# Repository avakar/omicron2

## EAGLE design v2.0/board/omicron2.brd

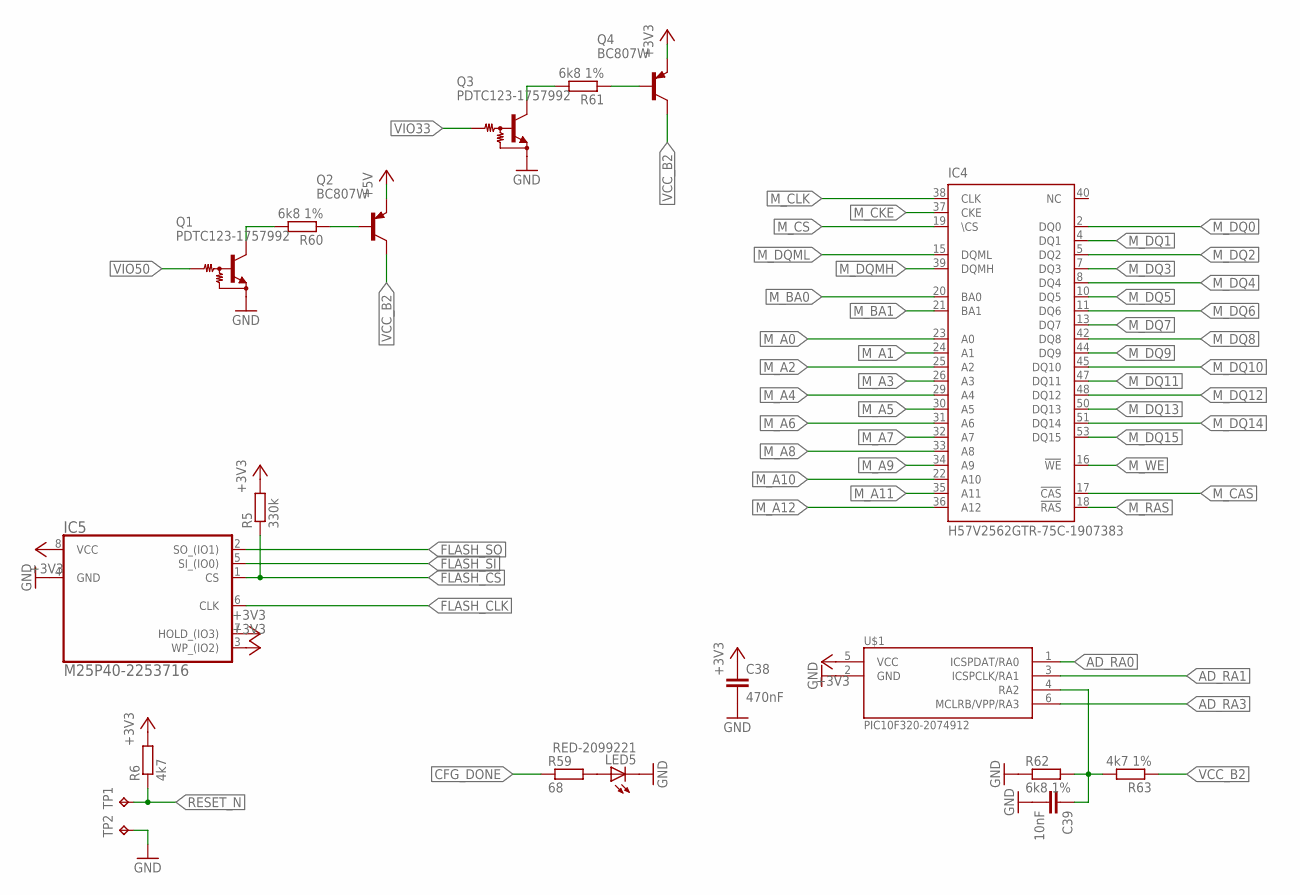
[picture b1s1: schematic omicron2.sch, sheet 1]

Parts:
C38: 470nF; C0603
C39: 10nF; C0603
IC4: H57V2562GTR-75C-1907383; TSOP54-400
IC5: M25P40-2253716; SO8
LED5: RED-2099221; CHIPLED_0603
Q1, Q3: PDTC123-1757992; SOT323
Q2, Q4: BC807W; SOT323-BEC
R5: 330k; R0603
R6: 4k7; R0603
R59: 68; R0603
R60, R61, R62: 6k8 1%; R0603
R63: 4k7 1%; R0603
TP1: TPTP15R; TP15R
TP2: TPTP20R; TP20R
U$1: PIC10F320-2074912; SOT23

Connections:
+3V3: C38.1, IC5.3 (WP_(IO2)), IC5.7 (HOLD_(IO3)), IC5.8 (VCC), Q4.2 (E), R5.2, R6.2, U$1.5 (VCC); also elsewhere on the board
+5V: Q2.2 (E); also elsewhere on the board
AD_RA0: U$1.1 (ICSPDAT/RA0); also elsewhere on the board
AD_RA1: U$1.3 (ICSPCLK/RA1); also elsewhere on the board
AD_RA3: U$1.6 (MCLRB/VPP/RA3); also elsewhere on the board
CFG_DONE: R59.1; also elsewhere on the board
FLASH_CLK: IC5.6 (CLK); also elsewhere on the board
FLASH_CS: IC5.1 (CS), R5.1; also elsewhere on the board
FLASH_SI: IC5.5 (SI_(IO0)); also elsewhere on the board
FLASH_SO: IC5.2 (SO_(IO1)); also elsewhere on the board
GND: C38.2, C39.2, IC5.4 (GND), LED5.C, Q1.2 (E), Q3.2 (E), R62.1, TP2.TP, U$1.2 (GND); also elsewhere on the board
M_A0: IC4.23 (A0); also elsewhere on the board
M_A1: IC4.24 (A1); also elsewhere on the board
M_A2: IC4.25 (A2); also elsewhere on the board
M_A3: IC4.26 (A3); also elsewhere on the board
M_A4: IC4.29 (A4); also elsewhere on the board
M_A5: IC4.30 (A5); also elsewhere on the board
M_A6: IC4.31 (A6); also elsewhere on the board
M_A7: IC4.32 (A7); also elsewhere on the board
M_A8: IC4.33 (A8); also elsewhere on the board
M_A9: IC4.34 (A9); also elsewhere on the board
M_A10: IC4.22 (A10); also elsewhere on the board
M_A11: IC4.35 (A11); also elsewhere on the board
M_A12: IC4.36 (A12); also elsewhere on the board
M_BA0: IC4.20 (BA0); also elsewhere on the board
M_BA1: IC4.21 (BA1); also elsewhere on the board
M_CAS: IC4.17 (!CAS); also elsewhere on the board
M_CKE: IC4.37 (CKE); also elsewhere on the board
M_CLK: IC4.38 (CLK); also elsewhere on the board
M_CS: IC4.19 (\CS); also elsewhere on the board
M_DQ0: IC4.2 (DQ0); also elsewhere on the board
M_DQ1: IC4.4 (DQ1); also elsewhere on the board
M_DQ2: IC4.5 (DQ2); also elsewhere on the board
M_DQ3: IC4.7 (DQ3); also elsewhere on the board
M_DQ4: IC4.8 (DQ4); also elsewhere on the board
M_DQ5: IC4.10 (DQ5); also elsewhere on the board
M_DQ6: IC4.11 (DQ6); also elsewhere on the board
M_DQ7: IC4.13 (DQ7); also elsewhere on the board
M_DQ8: IC4.42 (DQ8); also elsewhere on the board
M_DQ9: IC4.44 (DQ9); also elsewhere on the board
M_DQ10: IC4.45 (DQ10); also elsewhere on the board
M_DQ11: IC4.47 (DQ11); also elsewhere on the board
M_DQ12: IC4.48 (DQ12); also elsewhere on the board
M_DQ13: IC4.50 (DQ13); also elsewhere on the board
M_DQ14: IC4.51 (DQ14); also elsewhere on the board
M_DQ15: IC4.53 (DQ15); also elsewhere on the board
M_DQMH: IC4.39 (DQMH); also elsewhere on the board
M_DQML: IC4.15 (DQML); also elsewhere on the board
M_RAS: IC4.18 (!RAS); also elsewhere on the board
M_WE: IC4.16 (!WE); also elsewhere on the board
unnamed: LED5.A, R59.2
unnamed: Q2.1 (B), R60.1
unnamed: Q1.3 (C), R60.2
unnamed: Q4.1 (B), R61.1
unnamed: Q3.3 (C), R61.2
unnamed: C39.1, R62.2, R63.2, U$1.4 (RA2)
RESET_N: R6.1, TP1.TP; also elsewhere on the board
VCC_B2: Q2.3 (C), Q4.3 (C), R63.1; also elsewhere on the board
VIO33: Q3.1 (B); also elsewhere on the board
VIO50: Q1.1 (B); also elsewhere on the board

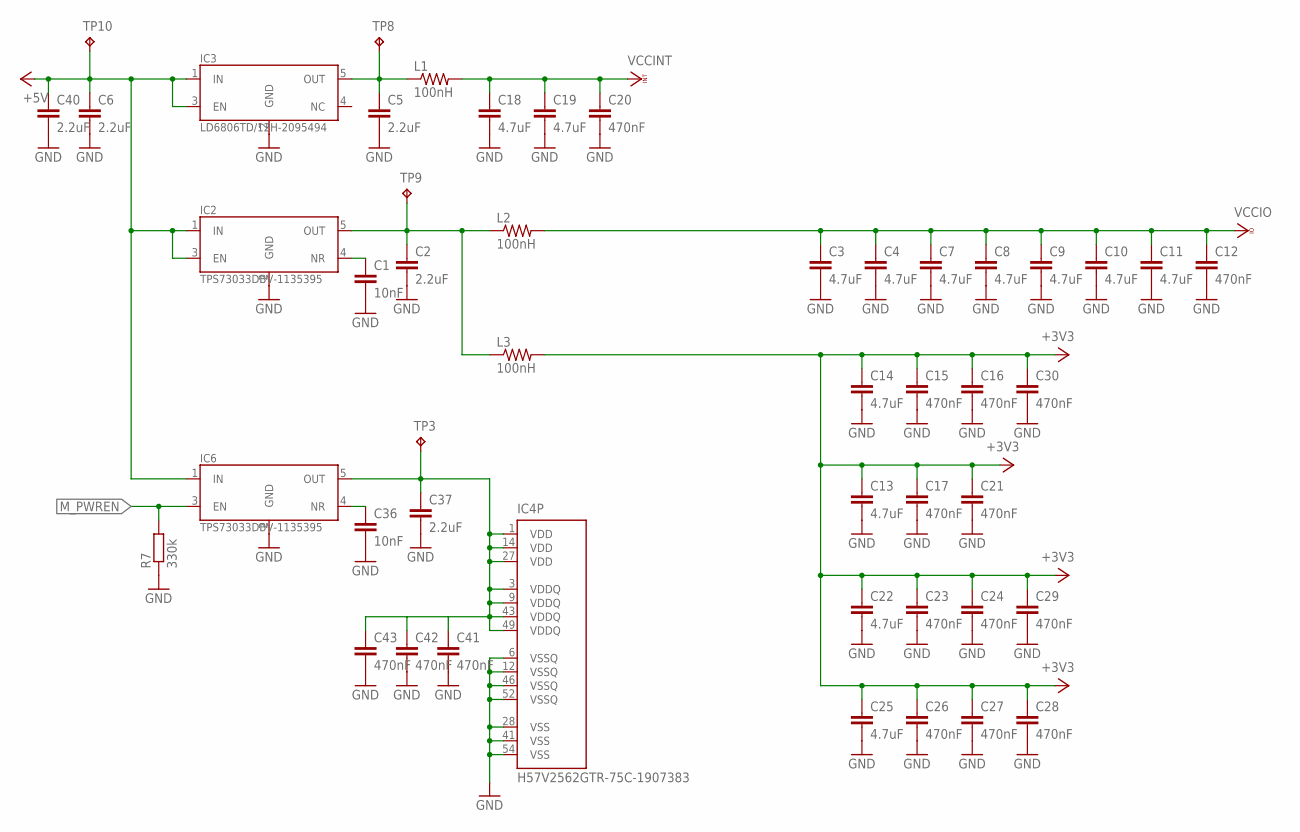
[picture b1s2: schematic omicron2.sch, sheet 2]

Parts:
C1, C36: 10nF; C0603
C2, C5, C6, C37, C40: 2.2uF; C0603
C3, C4, C7, C8, C9, C10, C11, C13, C14, C18, C19, C22, C25: 4.7uF; C0603
C12, C15, C16, C17, C20, C21, C23, C24, C26, C27, C28, C29, C30, C41, C42, C43: 470nF; C0603
IC2, IC6: TPS73033DBV-1135395; SOT23-DBV
IC3: LD6806TD/12H-2095494; SOT23-DBV
IC4: H57V2562GTR-75C-1907383; TSOP54-400
L1, L2, L3: 100nH; R0805
R7: 330k; R0603
TP3, TP8, TP9, TP10: TPTP15R; TP15R

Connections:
+3V3: C13.1, C14.1, C15.1, C16.1, C17.1, C21.1, C22.1, C23.1, C24.1, C25.1, C26.1, C27.1, C28.1, C29.1, C30.1, L3.2; also elsewhere on the board
+5V: C6.1, C40.1, IC2.1 (IN), IC2.3 (EN), IC3.1 (IN), IC3.3 (EN), IC6.1 (IN), TP10.TP; also elsewhere on the board
GND: C1.2, C2.2, C3.2, C4.2, C5.2, C6.2, C7.2, C8.2, C9.2, C10.2, C11.2, C12.2, C13.2, C14.2, C15.2, C16.2, C17.2, C18.2, C19.2, C20.2, C21.2, C22.2, C23.2, C24.2, C25.2, C26.2, C27.2, C28.2, C29.2, C30.2, C36.2, C37.2, C40.2, C41.2, C42.2, C43.2, IC2.2 (GND), IC3.2 (GND), IC4.6 (VSSQ), IC4.12 (VSSQ), IC4.28 (VSS), IC4.41 (VSS), IC4.46 (VSSQ), IC4.52 (VSSQ), IC4.54 (VSS), IC6.2 (GND), R7.1; also elsewhere on the board
M_PWREN: IC6.3 (EN), R7.2; also elsewhere on the board
unnamed: C1.1, IC2.4 (NR)
unnamed: C5.1, IC3.5 (OUT), L1.1, TP8.TP
unnamed: C2.1, IC2.5 (OUT), L2.1, L3.1, TP9.TP
unnamed: C36.1, IC6.4 (NR)
VCCINT: C18.1, C19.1, C20.1, L1.2; also elsewhere on the board
VCCIO: C3.1, C4.1, C7.1, C8.1, C9.1, C10.1, C11.1, C12.1, L2.2; also elsewhere on the board
VCC_MEM: C37.1, C41.1, C42.1, C43.1, IC4.1 (VDD), IC4.3 (VDDQ), IC4.9 (VDDQ), IC4.14 (VDD), IC4.27 (VDD), IC4.43 (VDDQ), IC4.49 (VDDQ), IC6.5 (OUT), TP3.TP

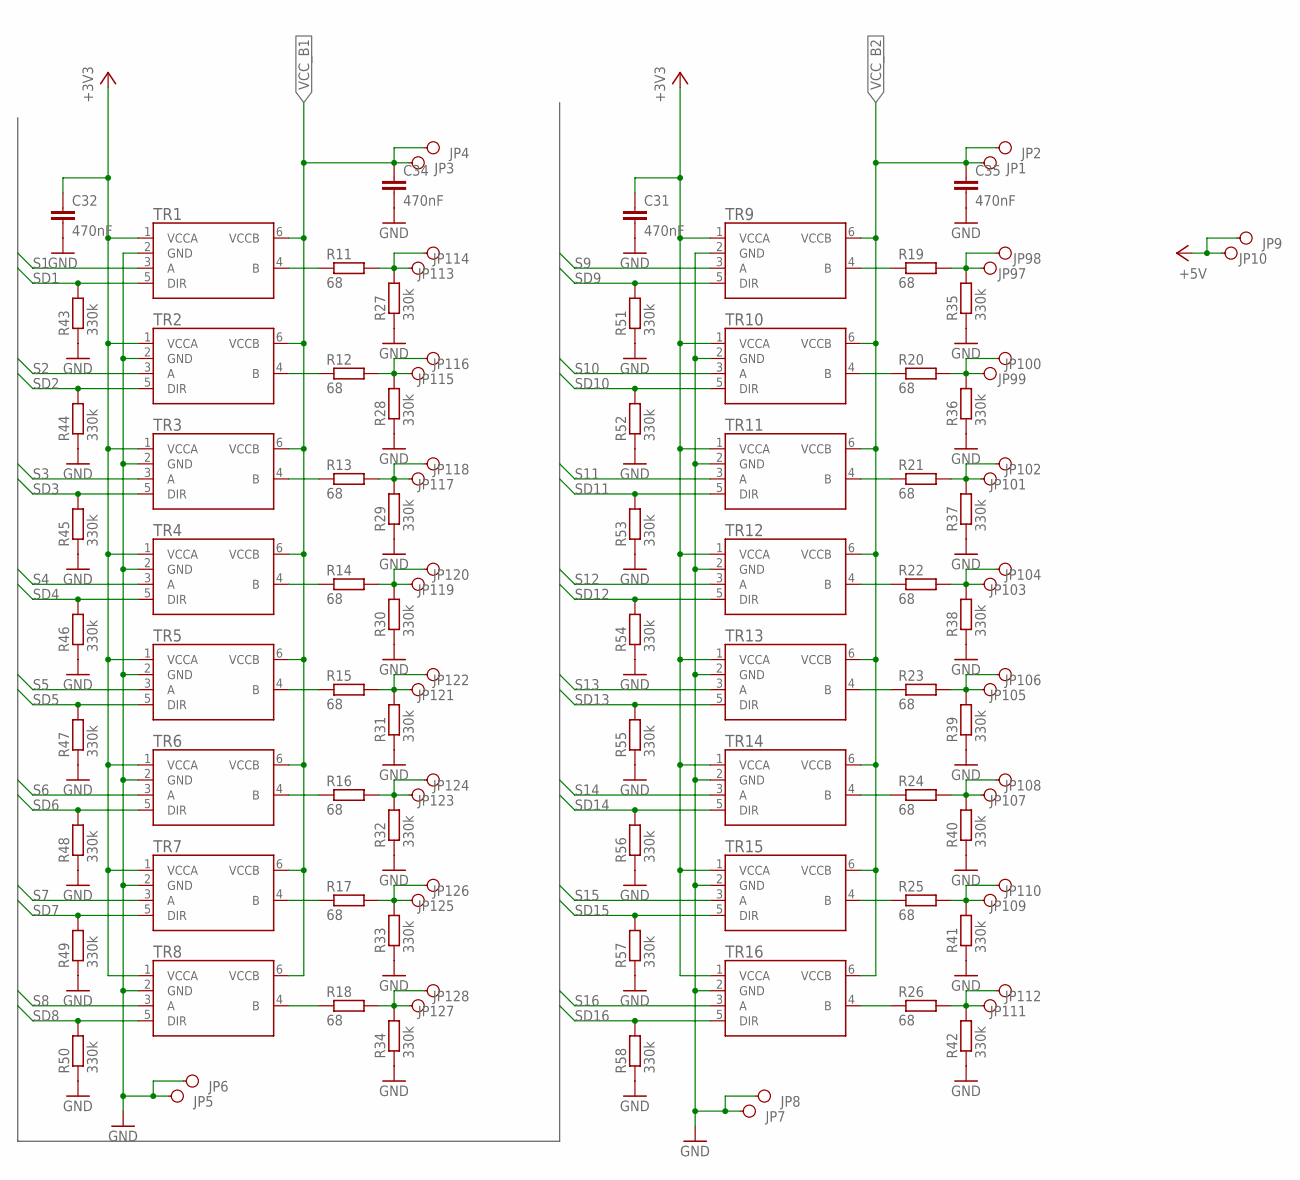
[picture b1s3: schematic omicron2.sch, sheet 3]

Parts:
C31, C32, C34, C35: 470nF; C0603
JP1, JP2, JP3, JP4, JP5, JP6, JP7, JP8, JP9, JP10, JP97, JP98, JP99, JP100, JP101, JP102, JP103, JP104, JP105, JP106, JP107, JP108, JP109, JP110, JP111, JP112, JP113, JP114, JP115, JP116, JP117, JP118, JP119, JP120, JP121, JP122, JP123, JP124, JP125, JP126, JP127, JP128: PINH1X01SMD
R11, R12, R13, R14, R15, R16, R17, R18, R19, R20, R21, R22, R23, R24, R25, R26: 68; R0603
R27, R28, R29, R30, R31, R32, R33, R34, R35, R36, R37, R38, R39, R40, R41, R42, R43, R44, R45, R46, R47, R48, R49, R50, R51, R52, R53, R54, R55, R56, R57, R58: 330k; R0603
TR1, TR2, TR3, TR4, TR5, TR6, TR7, TR8, TR9, TR10, TR11, TR12, TR13, TR14, TR15, TR16: 74LVC1T45DBV; SOT236

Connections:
+3V3: C31.1, C32.1, TR1.1 (VCCA), TR2.1 (VCCA), TR3.1 (VCCA), TR4.1 (VCCA), TR5.1 (VCCA), TR6.1 (VCCA), TR7.1 (VCCA), TR8.1 (VCCA), TR9.1 (VCCA), TR10.1 (VCCA), TR11.1 (VCCA), TR12.1 (VCCA), TR13.1 (VCCA), TR14.1 (VCCA), TR15.1 (VCCA), TR16.1 (VCCA); also elsewhere on the board
+5V: JP9.1, JP10.1; also elsewhere on the board
GND: C31.2, C32.2, C34.2, C35.2, JP5.1, JP6.1, JP7.1, JP8.1, R27.1, R28.1, R29.1, R30.1, R31.1, R32.1, R33.1, R34.1, R35.1, R36.1, R37.1, R38.1, R39.1, R40.1, R41.1, R42.1, R43.1, R44.1, R45.1, R46.1, R47.1, R48.1, R49.1, R50.1, R51.1, R52.1, R53.1, R54.1, R55.1, R56.1, R57.1, R58.1, TR1.2 (GND), TR2.2 (GND), TR3.2 (GND), TR4.2 (GND), TR5.2 (GND), TR6.2 (GND), TR7.2 (GND), TR8.2 (GND), TR9.2 (GND), TR10.2 (GND), TR11.2 (GND), TR12.2 (GND), TR13.2 (GND), TR14.2 (GND), TR15.2 (GND), TR16.2 (GND); also elsewhere on the board
IO1: JP113.1, JP114.1, R11.2, R27.2
IO2: JP115.1, JP116.1, R12.2, R28.2
IO3: JP117.1, JP118.1, R13.2, R29.2
IO4: JP119.1, JP120.1, R14.2, R30.2
IO5: JP121.1, JP122.1, R15.2, R31.2
IO6: JP123.1, JP124.1, R16.2, R32.2
IO7: JP125.1, JP126.1, R17.2, R33.2
IO8: JP127.1, JP128.1, R18.2, R34.2
IO9: JP97.1, JP98.1, R19.2, R35.2
IO10: JP99.1, JP100.1, R20.2, R36.2
IO11: JP101.1, JP102.1, R21.2, R37.2
IO12: JP103.1, JP104.1, R22.2, R38.2
IO13: JP105.1, JP106.1, R23.2, R39.2
IO14: JP107.1, JP108.1, R24.2, R40.2
IO15: JP109.1, JP110.1, R25.2, R41.2
IO16: JP111.1, JP112.1, R26.2, R42.2
unnamed: R11.1, TR1.4 (B)
unnamed: R12.1, TR2.4 (B)
unnamed: R13.1, TR3.4 (B)
unnamed: R14.1, TR4.4 (B)
unnamed: R15.1, TR5.4 (B)
unnamed: R16.1, TR6.4 (B)
unnamed: R17.1, TR7.4 (B)
unnamed: R18.1, TR8.4 (B)
unnamed: R19.1, TR9.4 (B)
unnamed: R20.1, TR10.4 (B)
unnamed: R21.1, TR11.4 (B)
unnamed: R22.1, TR12.4 (B)
unnamed: R23.1, TR13.4 (B)
unnamed: R24.1, TR14.4 (B)
unnamed: R25.1, TR15.4 (B)
unnamed: R26.1, TR16.4 (B)
S1: TR1.3 (A); also elsewhere on the board
S2: TR2.3 (A); also elsewhere on the board
S3: TR3.3 (A); also elsewhere on the board
S4: TR4.3 (A); also elsewhere on the board
S5: TR5.3 (A); also elsewhere on the board
S6: TR6.3 (A); also elsewhere on the board
S7: TR7.3 (A); also elsewhere on the board
S8: TR8.3 (A); also elsewhere on the board
S9: TR9.3 (A); also elsewhere on the board
S10: TR10.3 (A); also elsewhere on the board
S11: TR11.3 (A); also elsewhere on the board
S12: TR12.3 (A); also elsewhere on the board
S13: TR13.3 (A); also elsewhere on the board
S14: TR14.3 (A); also elsewhere on the board
S15: TR15.3 (A); also elsewhere on the board
S16: TR16.3 (A); also elsewhere on the board
SD1: R43.2, TR1.5 (DIR); also elsewhere on the board
SD2: R44.2, TR2.5 (DIR); also elsewhere on the board
SD3: R45.2, TR3.5 (DIR); also elsewhere on the board
SD4: R46.2, TR4.5 (DIR); also elsewhere on the board
SD5: R47.2, TR5.5 (DIR); also elsewhere on the board
SD6: R48.2, TR6.5 (DIR); also elsewhere on the board
SD7: R49.2, TR7.5 (DIR); also elsewhere on the board
SD8: R50.2, TR8.5 (DIR); also elsewhere on the board
SD9: R51.2, TR9.5 (DIR); also elsewhere on the board
SD10: R52.2, TR10.5 (DIR); also elsewhere on the board
SD11: R53.2, TR11.5 (DIR); also elsewhere on the board
SD12: R54.2, TR12.5 (DIR); also elsewhere on the board
SD13: R55.2, TR13.5 (DIR); also elsewhere on the board
SD14: R56.2, TR14.5 (DIR); also elsewhere on the board
SD15: R57.2, TR15.5 (DIR); also elsewhere on the board
SD16: R58.2, TR16.5 (DIR); also elsewhere on the board
VCC_B1: C34.1, JP3.1, JP4.1, TR1.6 (VCCB), TR2.6 (VCCB), TR3.6 (VCCB), TR4.6 (VCCB), TR5.6 (VCCB), TR6.6 (VCCB), TR7.6 (VCCB), TR8.6 (VCCB)
VCC_B2: C35.1, JP1.1, JP2.1, TR9.6 (VCCB), TR10.6 (VCCB), TR11.6 (VCCB), TR12.6 (VCCB), TR13.6 (VCCB), TR14.6 (VCCB), TR15.6 (VCCB), TR16.6 (VCCB); also elsewhere on the board

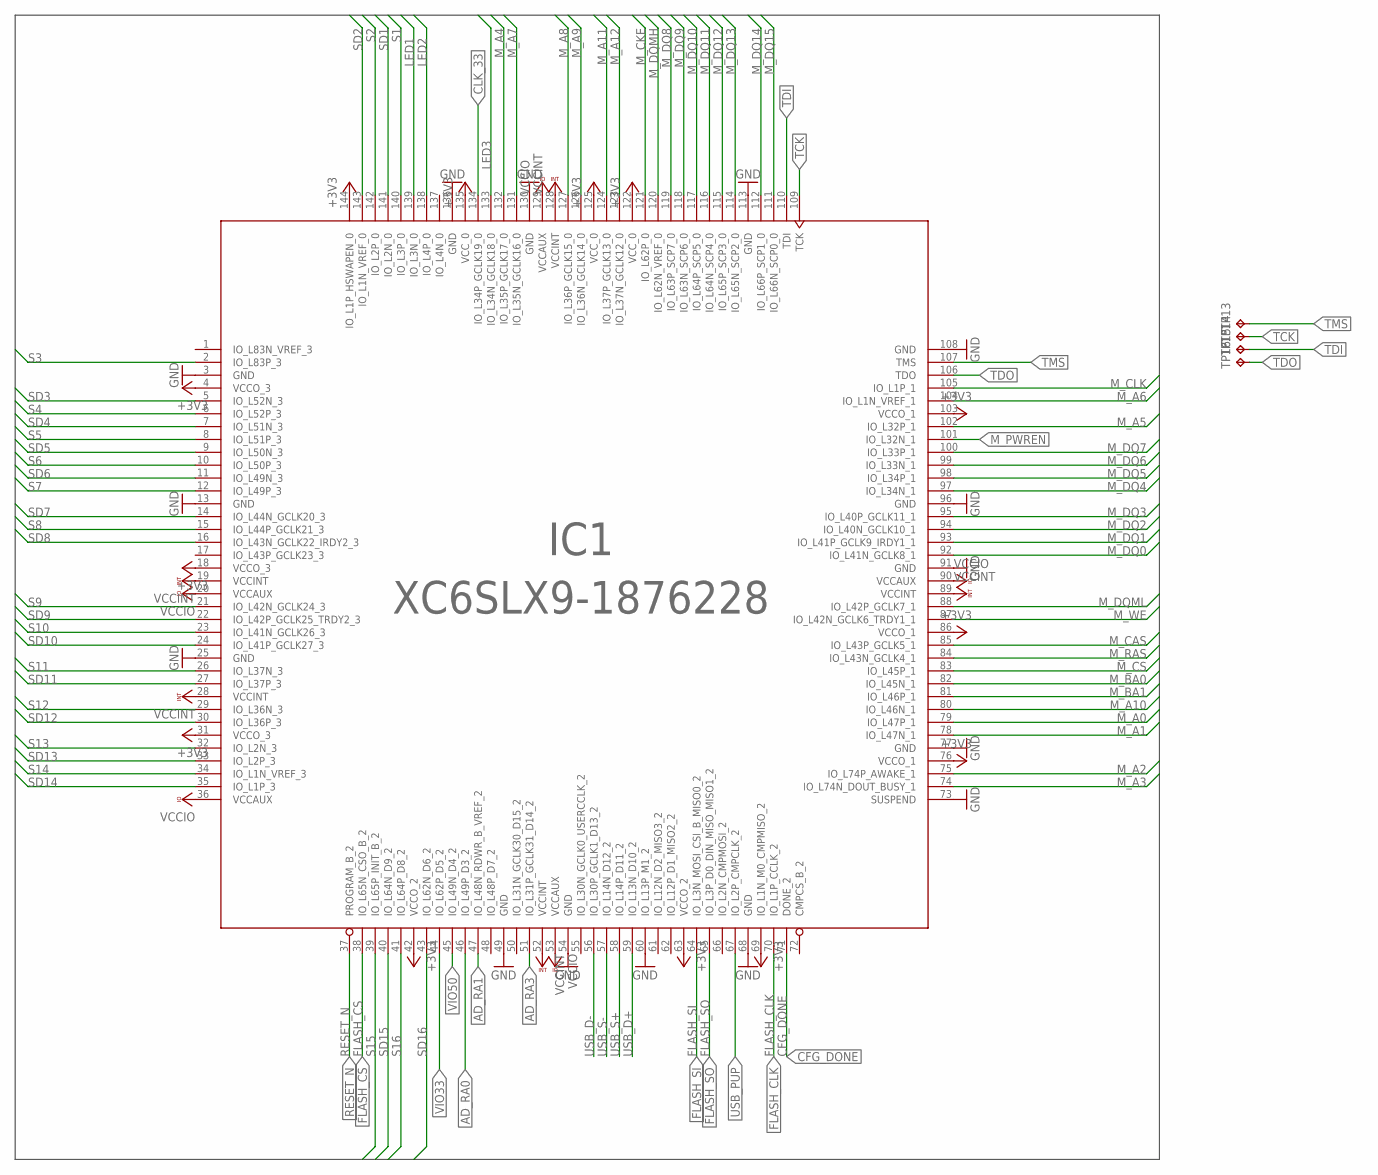
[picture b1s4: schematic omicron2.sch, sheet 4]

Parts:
IC1: XC6SLX9-1876228; TQG144
TP13, TP14, TP15, TP16: TPTP20R; TP20R

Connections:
+3V3: IC1.4 (VCCO_3), IC1.18 (VCCO_3), IC1.31 (VCCO_3), IC1.42 (VCCO_2), IC1.63 (VCCO_2), IC1.69 (IO_L1N_M0_CMPMISO_2), IC1.76 (VCCO_1), IC1.86 (VCCO_1), IC1.103 (VCCO_1), IC1.122 (VCC_0), IC1.125 (VCC_0), IC1.135 (VCC_0), IC1.144 (IO_L1P_HSWAPEN_0); also elsewhere on the board
AD_RA0: IC1.46 (IO_L49P_D3_2); also elsewhere on the board
AD_RA1: IC1.47 (IO_L48N_RDWR_B_VREF_2); also elsewhere on the board
AD_RA3: IC1.51 (IO_L31P_GCLK31_D14_2); also elsewhere on the board
CFG_DONE: IC1.71 (DONE_2); also elsewhere on the board
CLK_33: IC1.134 (IO_L34P_GCLK19_0); also elsewhere on the board
FLASH_CLK: IC1.70 (IO_L1P_CCLK_2); also elsewhere on the board
FLASH_CS: IC1.38 (IO_L65N_CSO_B_2); also elsewhere on the board
FLASH_SI: IC1.64 (IO_L3N_MOSI_CSI_B_MISO0_2); also elsewhere on the board
FLASH_SO: IC1.65 (IO_L3P_D0_DIN_MISO_MISO1_2); also elsewhere on the board
GND: IC1.3 (GND), IC1.13 (GND), IC1.25 (GND), IC1.49 (GND), IC1.54 (GND), IC1.60 (IO_L13P_M1_2), IC1.68 (GND), IC1.73 (SUSPEND), IC1.77 (GND), IC1.91 (GND), IC1.96 (GND), IC1.108 (GND), IC1.113 (GND), IC1.130 (GND), IC1.136 (GND); also elsewhere on the board
LED1: IC1.139 (IO_L3N_0); also elsewhere on the board
LED2: IC1.138 (IO_L4P_0); also elsewhere on the board
LED3: IC1.133 (IO_L34N_GCLK18_0); also elsewhere on the board
M_A0: IC1.79 (IO_L47P_1); also elsewhere on the board
M_A1: IC1.78 (IO_L47N_1); also elsewhere on the board
M_A2: IC1.75 (IO_L74P_AWAKE_1); also elsewhere on the board
M_A3: IC1.74 (IO_L74N_DOUT_BUSY_1); also elsewhere on the board
M_A4: IC1.132 (IO_L35P_GCLK17_0); also elsewhere on the board
M_A5: IC1.102 (IO_L32P_1); also elsewhere on the board
M_A6: IC1.104 (IO_L1N_VREF_1); also elsewhere on the board
M_A7: IC1.131 (IO_L35N_GCLK16_0); also elsewhere on the board
M_A8: IC1.127 (IO_L36P_GCLK15_0); also elsewhere on the board
M_A9: IC1.126 (IO_L36N_GCLK14_0); also elsewhere on the board
M_A10: IC1.80 (IO_L46N_1); also elsewhere on the board
M_A11: IC1.124 (IO_L37P_GCLK13_0); also elsewhere on the board
M_A12: IC1.123 (IO_L37N_GCLK12_0); also elsewhere on the board
M_BA0: IC1.82 (IO_L45N_1); also elsewhere on the board
M_BA1: IC1.81 (IO_L46P_1); also elsewhere on the board
M_CAS: IC1.85 (IO_L43P_GCLK5_1); also elsewhere on the board
M_CKE: IC1.121 (IO_L62P_0); also elsewhere on the board
M_CLK: IC1.105 (IO_L1P_1); also elsewhere on the board
M_CS: IC1.83 (IO_L45P_1); also elsewhere on the board
M_DQ0: IC1.92 (IO_L41N_GCLK8_1); also elsewhere on the board
M_DQ1: IC1.93 (IO_L41P_GCLK9_IRDY1_1); also elsewhere on the board
M_DQ2: IC1.94 (IO_L40N_GCLK10_1); also elsewhere on the board
M_DQ3: IC1.95 (IO_L40P_GCLK11_1); also elsewhere on the board
M_DQ4: IC1.97 (IO_L34N_1); also elsewhere on the board
M_DQ5: IC1.98 (IO_L34P_1); also elsewhere on the board
M_DQ6: IC1.99 (IO_L33N_1); also elsewhere on the board
M_DQ7: IC1.100 (IO_L33P_1); also elsewhere on the board
M_DQ8: IC1.119 (IO_L63P_SCP7_0); also elsewhere on the board
M_DQ9: IC1.118 (IO_L63N_SCP6_0); also elsewhere on the board
M_DQ10: IC1.117 (IO_L64P_SCP5_0); also elsewhere on the board
M_DQ11: IC1.116 (IO_L64N_SCP4_0); also elsewhere on the board
M_DQ12: IC1.115 (IO_L65P_SCP3_0); also elsewhere on the board
M_DQ13: IC1.114 (IO_L65N_SCP2_0); also elsewhere on the board
M_DQ14: IC1.112 (IO_L66P_SCP1_0); also elsewhere on the board
M_DQ15: IC1.111 (IO_L66N_SCP0_0); also elsewhere on the board
M_DQMH: IC1.120 (IO_L62N_VREF_0); also elsewhere on the board
M_DQML: IC1.88 (IO_L42P_GCLK7_1); also elsewhere on the board
M_PWREN: IC1.101 (IO_L32N_1); also elsewhere on the board
M_RAS: IC1.84 (IO_L43N_GCLK4_1); also elsewhere on the board
M_WE: IC1.87 (IO_L42N_GCLK6_TRDY1_1); also elsewhere on the board
RESET_N: IC1.37 (PROGRAM_B_2); also elsewhere on the board
S1: IC1.140 (IO_L3P_0); also elsewhere on the board
S2: IC1.142 (IO_L2P_0); also elsewhere on the board
S3: IC1.2 (IO_L83P_3); also elsewhere on the board
S4: IC1.6 (IO_L52P_3); also elsewhere on the board
S5: IC1.8 (IO_L51P_3); also elsewhere on the board
S6: IC1.10 (IO_L50P_3); also elsewhere on the board
S7: IC1.12 (IO_L49P_3); also elsewhere on the board
S8: IC1.15 (IO_L44P_GCLK21_3); also elsewhere on the board
S9: IC1.21 (IO_L42N_GCLK24_3); also elsewhere on the board
S10: IC1.23 (IO_L41N_GCLK26_3); also elsewhere on the board
S11: IC1.26 (IO_L37N_3); also elsewhere on the board
S12: IC1.29 (IO_L36N_3); also elsewhere on the board
S13: IC1.32 (IO_L2N_3); also elsewhere on the board
S14: IC1.34 (IO_L1N_VREF_3); also elsewhere on the board
S15: IC1.39 (IO_L65P_INIT_B_2); also elsewhere on the board
S16: IC1.41 (IO_L64P_D8_2); also elsewhere on the board
SD1: IC1.141 (IO_L2N_0); also elsewhere on the board
SD2: IC1.143 (IO_L1N_VREF_0); also elsewhere on the board
SD3: IC1.5 (IO_L52N_3); also elsewhere on the board
SD4: IC1.7 (IO_L51N_3); also elsewhere on the board
SD5: IC1.9 (IO_L50N_3); also elsewhere on the board
SD6: IC1.11 (IO_L49N_3); also elsewhere on the board
SD7: IC1.14 (IO_L44N_GCLK20_3); also elsewhere on the board
SD8: IC1.16 (IO_L43N_GCLK22_IRDY2_3); also elsewhere on the board
SD9: IC1.22 (IO_L42P_GCLK25_TRDY2_3); also elsewhere on the board
SD10: IC1.24 (IO_L41P_GCLK27_3); also elsewhere on the board
SD11: IC1.27 (IO_L37P_3); also elsewhere on the board
SD12: IC1.30 (IO_L36P_3); also elsewhere on the board
SD13: IC1.33 (IO_L2P_3); also elsewhere on the board
SD14: IC1.35 (IO_L1P_3); also elsewhere on the board
SD15: IC1.40 (IO_L64N_D9_2); also elsewhere on the board
SD16: IC1.43 (IO_L62N_D6_2); also elsewhere on the board
TCK: IC1.109 (TCK), TP14.TP
TDI: IC1.110 (TDI), TP15.TP
TDO: IC1.106 (TDO), TP16.TP
TMS: IC1.107 (TMS), TP13.TP
USB_D+: IC1.59 (IO_L13N_D10_2); also elsewhere on the board
USB_D-: IC1.56 (IO_L30P_GCLK1_D13_2); also elsewhere on the board
USB_PUP: IC1.67 (IO_L2P_CMPCLK_2); also elsewhere on the board
USB_S+: IC1.58 (IO_L14P_D11_2); also elsewhere on the board
USB_S-: IC1.57 (IO_L14N_D12_2); also elsewhere on the board
VCCINT: IC1.19 (VCCINT), IC1.28 (VCCINT), IC1.52 (VCCINT), IC1.89 (VCCINT), IC1.128 (VCCINT); also elsewhere on the board
VCCIO: IC1.20 (VCCAUX), IC1.36 (VCCAUX), IC1.53 (VCCAUX), IC1.90 (VCCAUX), IC1.129 (VCCAUX); also elsewhere on the board
VIO33: IC1.44 (IO_L62P_D5_2); also elsewhere on the board
VIO50: IC1.45 (IO_L49N_D4_2); also elsewhere on the board

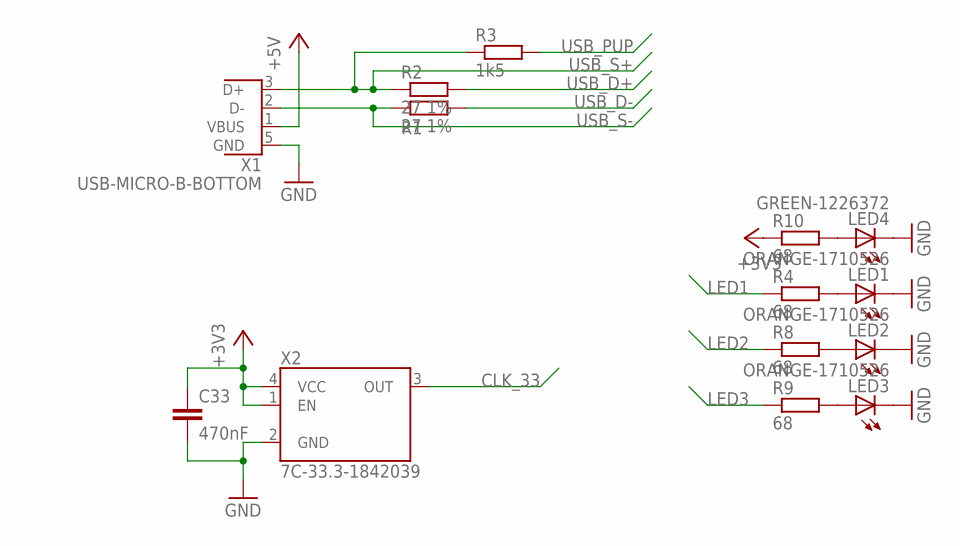
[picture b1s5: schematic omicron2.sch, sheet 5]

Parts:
C33: 470nF; C0603
LED1, LED2, LED3: ORANGE-1710526; CHIPLED_0603
LED4: GREEN-1226372; CHIPLED_0603
R1, R2: 27 1%; R0603
R3: 1k5; R0603
R4, R8, R9, R10: 68; R0603
X1: USB-MICRO-B-BOTTOM; USB-MICRO-B-BOTTOM-MOLEX
X2: 7C-33.3-1842039; 5X3.2_HAND

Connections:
+3V3: C33.1, R10.1, X2.1 (EN), X2.4 (VCC); also elsewhere on the board
+5V: X1.1 (VBUS); also elsewhere on the board
CLK_33: X2.3 (OUT); also elsewhere on the board
GND: C33.2, LED1.C, LED2.C, LED3.C, LED4.C, X1.5 (GND), X2.2 (GND); also elsewhere on the board
LED1: R4.1; also elsewhere on the board
LED2: R8.1; also elsewhere on the board
LED3: R9.1; also elsewhere on the board
unnamed: LED1.A, R4.2
unnamed: LED2.A, R8.2
unnamed: LED3.A, R9.2
unnamed: LED4.A, R10.2
USB_D+: R2.2; also elsewhere on the board
USB_D-: R1.2; also elsewhere on the board
USB_PUP: R3.2; also elsewhere on the board
USB_S+: R2.1, R3.1, X1.3 (D+); also elsewhere on the board
USB_S-: R1.1, X1.2 (D-); also elsewhere on the board

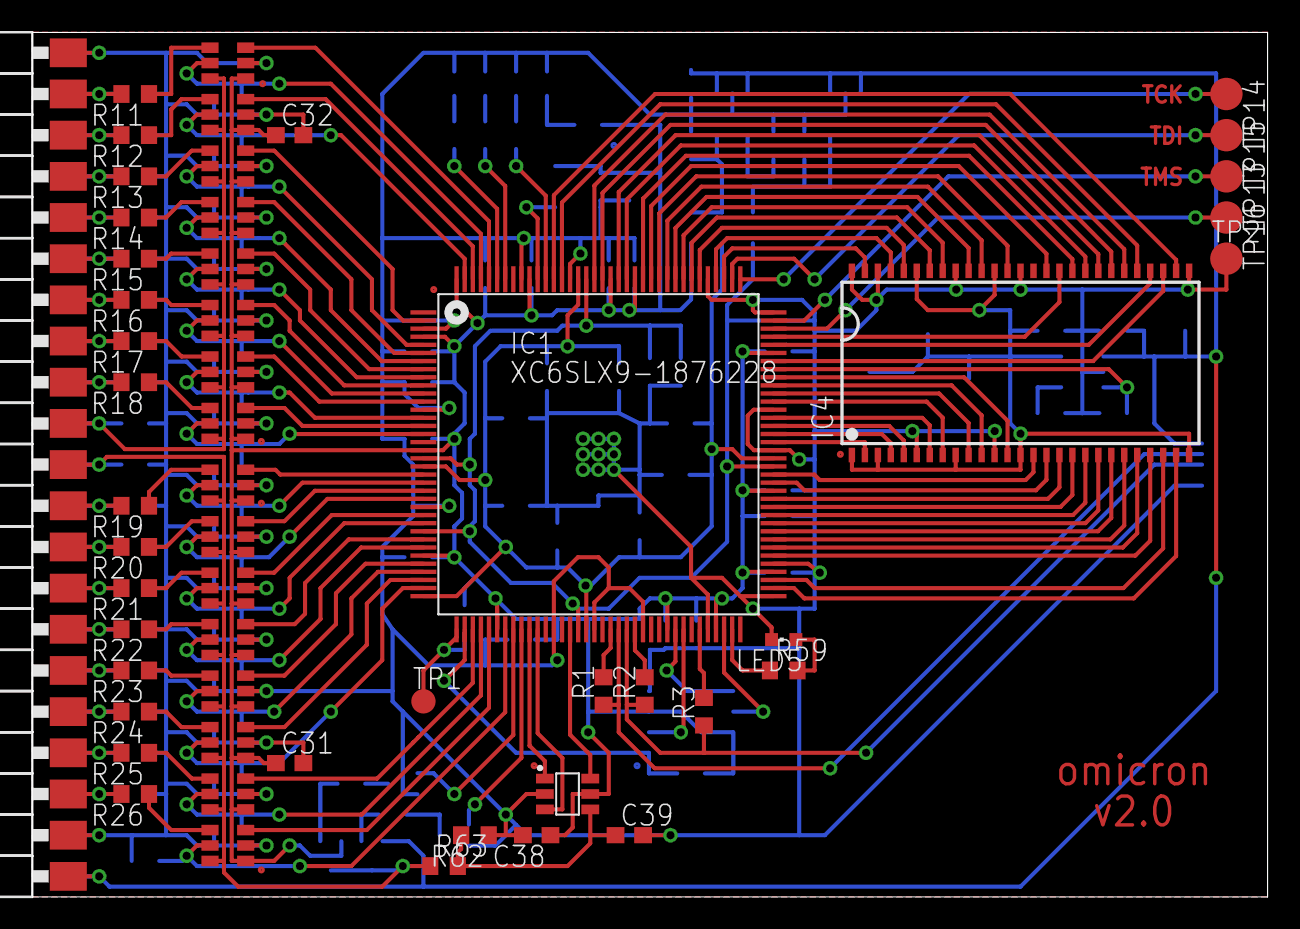
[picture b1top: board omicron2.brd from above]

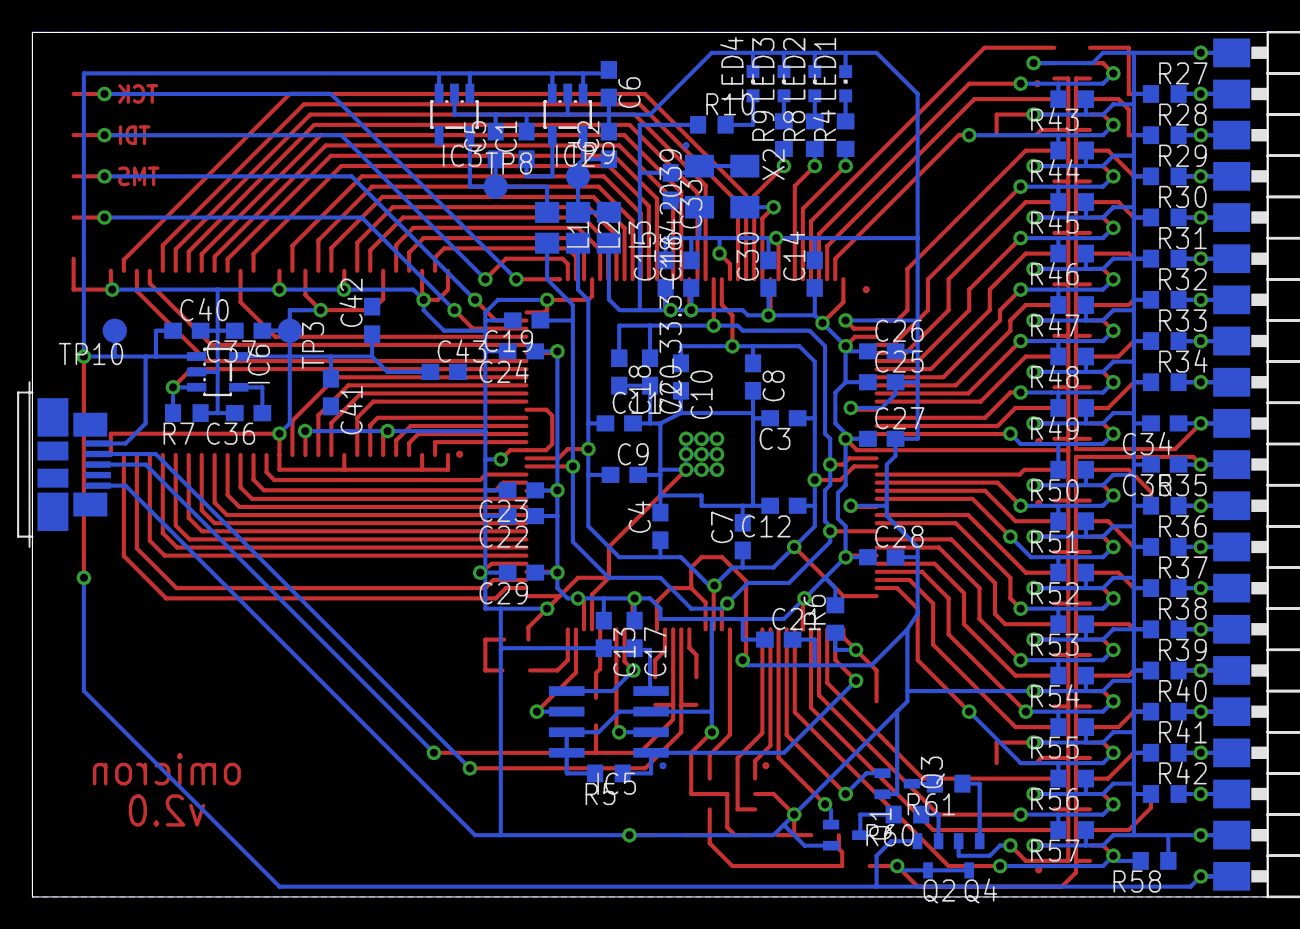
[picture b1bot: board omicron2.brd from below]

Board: 2 copper layers, 76.2 x 53.3 mm, 195 parts (122 on the bottom side), 150 nets.

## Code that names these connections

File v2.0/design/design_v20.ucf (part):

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NET "led[0]" LOC = P139;
NET "led[1]" LOC = P138;
NET "led[2]" LOC = P133;
NET "clk_33" LOC = P134;


NET "flash_clk" LOC = P70;
NET "flash_cs" LOC = P38;
NET "flash_si" LOC = P64;
NET "flash_so" LOC = P65;


NET "s[0]" LOC = P140;
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NET "sd[2]" DRIVE = 12;
NET "sd[1]" DRIVE = 12;
NET "sd[0]" DRIVE = 12;
NET "clk_33" DRIVE = 12;
NET "led[2]" SLEW = SLOW;
NET "led[1]" SLEW = SLOW;
NET "led[0]" SLEW = SLOW;
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NET "flash_cs" IOSTANDARD = LVCMOS33;
NET "flash_si" IOSTANDARD = LVCMOS33;
NET "flash_so" IOSTANDARD = LVCMOS33;
NET "flash_clk" DRIVE = 12;
NET "flash_cs" DRIVE = 12;
NET "flash_si" DRIVE = 12;
NET "flash_so" DRIVE = 12;
NET "flash_clk" SLEW = SLOW;
NET "flash_cs" SLEW = SLOW;
NET "flash_si" SLEW = SLOW;
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NET "usb_sp" IOSTANDARD = LVDS_33;


NET "usb_pup" LOC = P67;
NET "usb_dp" LOC = P59;
NET "usb_dn" LOC = P56;

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NET "usb_pup" IOSTANDARD = LVCMOS33;


NET "m_clk" LOC = P105;
NET "m_cs_n" LOC = P83;
NET "m_cke" LOC = P121;
NET "m_cas_n" LOC = P85;
NET "m_ras_n" LOC = P84;
NET "m_we_n" LOC = P87;
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NET "m_udqm" LOC = P120;

# PlanAhead Generated physical constraints 
NET "m_pwren" LOC = P101;

# PlanAhead Generated IO constraints 
NET "m_pwren" IOSTANDARD = LVCMOS33;
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
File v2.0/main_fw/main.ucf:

NET "clk_33" LOC = P134;


NET "clk_33" IOSTANDARD = LVCMOS33;


NET "led[0]" LOC = P139;
NET "led[1]" LOC = P138;
NET "led[2]" LOC = P133;


NET "led[2]" IOSTANDARD = LVCMOS33;
NET "led[1]" IOSTANDARD = LVCMOS33;
NET "led[0]" IOSTANDARD = LVCMOS33;


NET "usb_dp" LOC = P59;
NET "usb_dn" LOC = P56;
NET "usb_sp" LOC = P58;
NET "usb_pullup" LOC = P67;


NET "usb_sp" IOSTANDARD = LVDS_33;
NET "usb_pullup" IOSTANDARD = LVCMOS33;
NET "usb_dp" IOSTANDARD = LVCMOS33;
NET "usb_dn" IOSTANDARD = LVCMOS33;


NET "vio50" LOC = P45;
NET "vio33" LOC = P44;


NET "vio33" IOSTANDARD = LVCMOS33;
NET "vio50" IOSTANDARD = LVCMOS33;

NET "spi_clk" LOC = P70;
NET "spi_mosi" LOC = P64;
NET "spi_miso" LOC = P65;
NET "spi_cs" LOC = P38;


NET "spi_clk" IOSTANDARD = LVCMOS33;
NET "spi_cs" IOSTANDARD = LVCMOS33;
NET "spi_miso" IOSTANDARD = LVCMOS33;
NET "spi_mosi" IOSTANDARD = LVCMOS33;
#Created by Constraints Editor (xc6slx9-tqg144-2) - 2014/09/07
NET "clk_33" TNM_NET = "clk_33";
TIMESPEC TS_clk_33 = PERIOD "clk_33" 30 ns HIGH 50 %;
NET "dna0_clk" TNM_NET = "dna0_clk";



NET "m_clk" LOC = P105;
NET "m_cs_n" LOC = P83;
NET "m_cke" LOC = P121;
NET "m_cas_n" LOC = P85;
NET "m_ras_n" LOC = P84;
NET "m_we_n" LOC = P87;


NET "m_cas_n" IOSTANDARD = LVCMOS33;
NET "m_cke" IOSTANDARD = LVCMOS33;
NET "m_clk" IOSTANDARD = LVCMOS33;
NET "m_cs_n" IOSTANDARD = LVCMOS33;
NET "m_ldqm" IOSTANDARD = LVCMOS33;
NET "m_ras_n" IOSTANDARD = LVCMOS33;
NET "m_udqm" IOSTANDARD = LVCMOS33;
NET "m_we_n" IOSTANDARD = LVCMOS33;


NET "m_a[0]" LOC = P79;
NET "m_a[1]" LOC = P78;
NET "m_a[2]" LOC = P75;
NET "m_a[3]" LOC = P74;
NET "m_a[4]" LOC = P132;
NET "m_a[5]" LOC = P102;
NET "m_a[6]" LOC = P104;
NET "m_a[7]" LOC = P131;
NET "m_a[8]" LOC = P127;
NET "m_a[9]" LOC = P126;
NET "m_a[10]" LOC = P80;
NET "m_a[11]" LOC = P124;
NET "m_a[12]" LOC = P123;


NET "m_a[12]" IOSTANDARD = LVCMOS33;
NET "m_a[11]" IOSTANDARD = LVCMOS33;
NET "m_a[10]" IOSTANDARD = LVCMOS33;
NET "m_a[9]" IOSTANDARD = LVCMOS33;
NET "m_a[8]" IOSTANDARD = LVCMOS33;
NET "m_a[7]" IOSTANDARD = LVCMOS33;
NET "m_a[6]" IOSTANDARD = LVCMOS33;
NET "m_a[5]" IOSTANDARD = LVCMOS33;
NET "m_a[4]" IOSTANDARD = LVCMOS33;
NET "m_a[3]" IOSTANDARD = LVCMOS33;
NET "m_a[2]" IOSTANDARD = LVCMOS33;
NET "m_a[1]" IOSTANDARD = LVCMOS33;
NET "m_a[0]" IOSTANDARD = LVCMOS33;
NET "m_ba[1]" IOSTANDARD = LVCMOS33;
NET "m_ba[0]" IOSTANDARD = LVCMOS33;
NET "m_dq[15]" IOSTANDARD = LVCMOS33;
NET "m_dq[14]" IOSTANDARD = LVCMOS33;
NET "m_dq[13]" IOSTANDARD = LVCMOS33;
NET "m_dq[12]" IOSTANDARD = LVCMOS33;
NET "m_dq[11]" IOSTANDARD = LVCMOS33;
NET "m_dq[10]" IOSTANDARD = LVCMOS33;
NET "m_dq[9]" IOSTANDARD = LVCMOS33;
NET "m_dq[8]" IOSTANDARD = LVCMOS33;
NET "m_dq[7]" IOSTANDARD = LVCMOS33;
NET "m_dq[6]" IOSTANDARD = LVCMOS33;
NET "m_dq[5]" IOSTANDARD = LVCMOS33;
NET "m_dq[4]" IOSTANDARD = LVCMOS33;
NET "m_dq[3]" IOSTANDARD = LVCMOS33;
NET "m_dq[2]" IOSTANDARD = LVCMOS33;
NET "m_dq[1]" IOSTANDARD = LVCMOS33;
NET "m_dq[0]" IOSTANDARD = LVCMOS33;


NET "m_ba[0]" LOC = P82;
NET "m_ba[1]" LOC = P81;
NET "m_dq[0]" LOC = P92;
NET "m_dq[1]" LOC = P93;
NET "m_dq[2]" LOC = P94;
NET "m_dq[3]" LOC = P95;
NET "m_dq[4]" LOC = P97;
NET "m_dq[5]" LOC = P98;
NET "m_dq[6]" LOC = P99;
NET "m_dq[7]" LOC = P100;
NET "m_dq[8]" LOC = P119;
NET "m_dq[9]" LOC = P118;
NET "m_dq[10]" LOC = P117;
NET "m_dq[11]" LOC = P116;
NET "m_dq[12]" LOC = P115;
NET "m_dq[13]" LOC = P114;
NET "m_dq[14]" LOC = P112;
NET "m_dq[15]" LOC = P111;
NET "m_ldqm" LOC = P88;
NET "m_udqm" LOC = P120;

NET "m_pwren" LOC = P101;

NET "m_pwren" IOSTANDARD = LVCMOS33;
NET "m_dq[15]" KEEPER;
NET "m_dq[14]" KEEPER;
NET "m_dq[13]" KEEPER;
NET "m_dq[12]" KEEPER;
NET "m_dq[11]" KEEPER;
NET "m_dq[10]" KEEPER;
NET "m_dq[9]" KEEPER;
NET "m_dq[8]" KEEPER;
NET "m_dq[7]" KEEPER;
NET "m_dq[6]" KEEPER;
NET "m_dq[5]" KEEPER;
NET "m_dq[4]" KEEPER;
NET "m_dq[3]" KEEPER;
NET "m_dq[2]" KEEPER;
NET "m_dq[1]" KEEPER;
NET "m_dq[0]" KEEPER;

INST "m_dq[0]" TNM = "m_dq_grp";
INST "m_dq[1]" TNM = "m_dq_grp";
INST "m_dq[2]" TNM = "m_dq_grp";
INST "m_dq[3]" TNM = "m_dq_grp";
INST "m_dq[4]" TNM = "m_dq_grp";
INST "m_dq[5]" TNM = "m_dq_grp";
INST "m_dq[6]" TNM = "m_dq_grp";
INST "m_dq[7]" TNM = "m_dq_grp";
INST "m_dq[8]" TNM = "m_dq_grp";
INST "m_dq[9]" TNM = "m_dq_grp";
INST "m_dq[10]" TNM = "m_dq_grp";
INST "m_dq[11]" TNM = "m_dq_grp";
INST "m_dq[12]" TNM = "m_dq_grp";
INST "m_dq[13]" TNM = "m_dq_grp";
INST "m_dq[14]" TNM = "m_dq_grp";
INST "m_dq[15]" TNM = "m_dq_grp";
INST "m_dq[0]" TNM = "m_out_grp";
INST "m_dq[1]" TNM = "m_out_grp";
INST "m_dq[2]" TNM = "m_out_grp";
INST "m_dq[3]" TNM = "m_out_grp";
INST "m_dq[4]" TNM = "m_out_grp";
INST "m_dq[5]" TNM = "m_out_grp";
INST "m_dq[6]" TNM = "m_out_grp";
INST "m_dq[7]" TNM = "m_out_grp";
INST "m_dq[8]" TNM = "m_out_grp";
INST "m_dq[9]" TNM = "m_out_grp";
INST "m_dq[10]" TNM = "m_out_grp";
INST "m_dq[11]" TNM = "m_out_grp";
INST "m_dq[12]" TNM = "m_out_grp";
INST "m_dq[13]" TNM = "m_out_grp";
INST "m_dq[14]" TNM = "m_out_grp";
INST "m_dq[15]" TNM = "m_out_grp";
INST "m_a[0]" TNM = "m_out_grp";
INST "m_a[1]" TNM = "m_out_grp";
INST "m_a[2]" TNM = "m_out_grp";
INST "m_a[3]" TNM = "m_out_grp";
INST "m_a[4]" TNM = "m_out_grp";
INST "m_a[5]" TNM = "m_out_grp";
INST "m_a[6]" TNM = "m_out_grp";
INST "m_a[7]" TNM = "m_out_grp";
INST "m_a[8]" TNM = "m_out_grp";
INST "m_a[9]" TNM = "m_out_grp";
INST "m_a[10]" TNM = "m_out_grp";
INST "m_a[11]" TNM = "m_out_grp";
INST "m_a[12]" TNM = "m_out_grp";
INST "m_we_n" TNM = "m_out_grp";
INST "m_ba[0]" TNM = "m_out_grp";
INST "m_ba[1]" TNM = "m_out_grp";
INST "m_cas_n" TNM = "m_out_grp";
INST "m_cke" TNM = "m_out_grp";
INST "m_clk" TNM = "m_out_grp";
INST "m_cs_n" TNM = "m_out_grp";
INST "m_ldqm" TNM = "m_out_grp";
INST "m_pwren" TNM = "m_out_grp";
INST "m_ras_n" TNM = "m_out_grp";
INST "m_udqm" TNM = "m_out_grp";

NET "clk_48" TNM_NET = "clk_48";
NET "clk_dram" TNM_NET = "clk_dram";
#NET "clk_sampler" TNM_NET = clk_sampler;

#TIMESPEC TS_cpu_to_sampler = FROM "clk_48" TO "clk_sampler" TIG;
#TIMESPEC TS_sampler_to_cpu = FROM "clk_sampler" TO "clk_48" TIG;
TIMESPEC TS_cpu_to_dram = FROM "clk_48" TO "clk_dram" TIG ;
TIMESPEC TS_dram_to_cpu = FROM "clk_dram" TO "clk_48" TIG ;


NET "pic_clk" LOC = P47;
NET "pic_data" LOC = P46;
NET "pic_mclr_n" LOC = P51;


NET "pic_clk" IOSTANDARD = LVCMOS33;
NET "pic_data" IOSTANDARD = LVCMOS33;
NET "pic_mclr_n" IOSTANDARD = LVCMOS33;


NET "pic_data" PULLDOWN;
NET "pic_clk" PULLDOWN;
NET "spi_miso" KEEPER;
NET "s[15]" KEEPER;
NET "s[14]" KEEPER;
NET "s[13]" KEEPER;
NET "s[12]" KEEPER;
NET "s[11]" KEEPER;
NET "s[10]" KEEPER;
NET "s[9]" KEEPER;
NET "s[8]" KEEPER;
NET "s[7]" KEEPER;
NET "s[6]" KEEPER;
NET "s[5]" KEEPER;
NET "s[4]" KEEPER;
NET "s[3]" KEEPER;
NET "s[2]" KEEPER;
NET "s[1]" KEEPER;
NET "s[0]" KEEPER;

# PlanAhead Generated IO constraints 

NET "s[15]" IOSTANDARD = LVCMOS33;
NET "s[14]" IOSTANDARD = LVCMOS33;
NET "s[13]" IOSTANDARD = LVCMOS33;
NET "s[12]" IOSTANDARD = LVCMOS33;
NET "s[11]" IOSTANDARD = LVCMOS33;
NET "s[10]" IOSTANDARD = LVCMOS33;
NET "s[9]" IOSTANDARD = LVCMOS33;
NET "s[8]" IOSTANDARD = LVCMOS33;
NET "s[7]" IOSTANDARD = LVCMOS33;
NET "s[6]" IOSTANDARD = LVCMOS33;
NET "s[5]" IOSTANDARD = LVCMOS33;
NET "s[4]" IOSTANDARD = LVCMOS33;
NET "s[3]" IOSTANDARD = LVCMOS33;
NET "s[2]" IOSTANDARD = LVCMOS33;
NET "s[1]" IOSTANDARD = LVCMOS33;
NET "s[0]" IOSTANDARD = LVCMOS33;
NET "sd[15]" IOSTANDARD = LVCMOS33;
NET "sd[14]" IOSTANDARD = LVCMOS33;
NET "sd[13]" IOSTANDARD = LVCMOS33;
NET "sd[12]" IOSTANDARD = LVCMOS33;
NET "sd[11]" IOSTANDARD = LVCMOS33;
NET "sd[10]" IOSTANDARD = LVCMOS33;
NET "sd[9]" IOSTANDARD = LVCMOS33;
NET "sd[8]" IOSTANDARD = LVCMOS33;
NET "sd[7]" IOSTANDARD = LVCMOS33;
NET "sd[6]" IOSTANDARD = LVCMOS33;
NET "sd[5]" IOSTANDARD = LVCMOS33;
NET "sd[4]" IOSTANDARD = LVCMOS33;
NET "sd[3]" IOSTANDARD = LVCMOS33;
NET "sd[2]" IOSTANDARD = LVCMOS33;
NET "sd[1]" IOSTANDARD = LVCMOS33;
NET "sd[0]" IOSTANDARD = LVCMOS33;

# PlanAhead Generated physical constraints 

NET "s[0]" LOC = P140;
NET "s[1]" LOC = P142;
NET "s[2]" LOC = P2;
NET "s[3]" LOC = P6;
NET "s[4]" LOC = P8;
NET "s[5]" LOC = P10;
NET "s[6]" LOC = P12;
NET "s[7]" LOC = P15;
NET "s[8]" LOC = P21;
NET "s[9]" LOC = P23;
NET "s[10]" LOC = P26;
NET "s[11]" LOC = P29;
NET "s[12]" LOC = P32;
NET "s[13]" LOC = P34;
NET "s[14]" LOC = P39;
NET "s[15]" LOC = P41;
NET "sd[0]" LOC = P141;
NET "sd[1]" LOC = P143;
NET "sd[2]" LOC = P5;
NET "sd[3]" LOC = P7;
NET "sd[4]" LOC = P9;
NET "sd[5]" LOC = P11;
NET "sd[6]" LOC = P14;
NET "sd[7]" LOC = P16;
NET "sd[8]" LOC = P22;
NET "sd[9]" LOC = P24;
NET "sd[10]" LOC = P27;
NET "sd[11]" LOC = P30;
NET "sd[12]" LOC = P33;
NET "sd[13]" LOC = P35;
NET "sd[14]" LOC = P40;
NET "sd[15]" LOC = P43;
